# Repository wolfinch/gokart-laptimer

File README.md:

#Gokart-LapTimer-iMproved (GLTiM) 1.0
---------
The GLTiM is built on top of the gokart-laptimer which uses IR beacon and Raspbery Pi as detector/Receiver. 
The GLT improved provides many more features than the previous version plus a more streamlined web interface.

1. Two way RF communication using Nordic NRF24L01+ RF chip between Control center and detector
2. Detector Supports Magnetic Strip as well as IR beacon
3. Detector is in Kart. Allows feedback for the driver (not implemented)
4. Raspberry Pi as control Center 

# gokart-laptimer 0.1
Open hardware-software project to setup a go kart lap timer and counter with IR as the trigger beacon. 

1. NEC pulse width IR protocol is used as the beacon protocol. 
2. Raspberry-Pi based controller.
3. php based GUI.

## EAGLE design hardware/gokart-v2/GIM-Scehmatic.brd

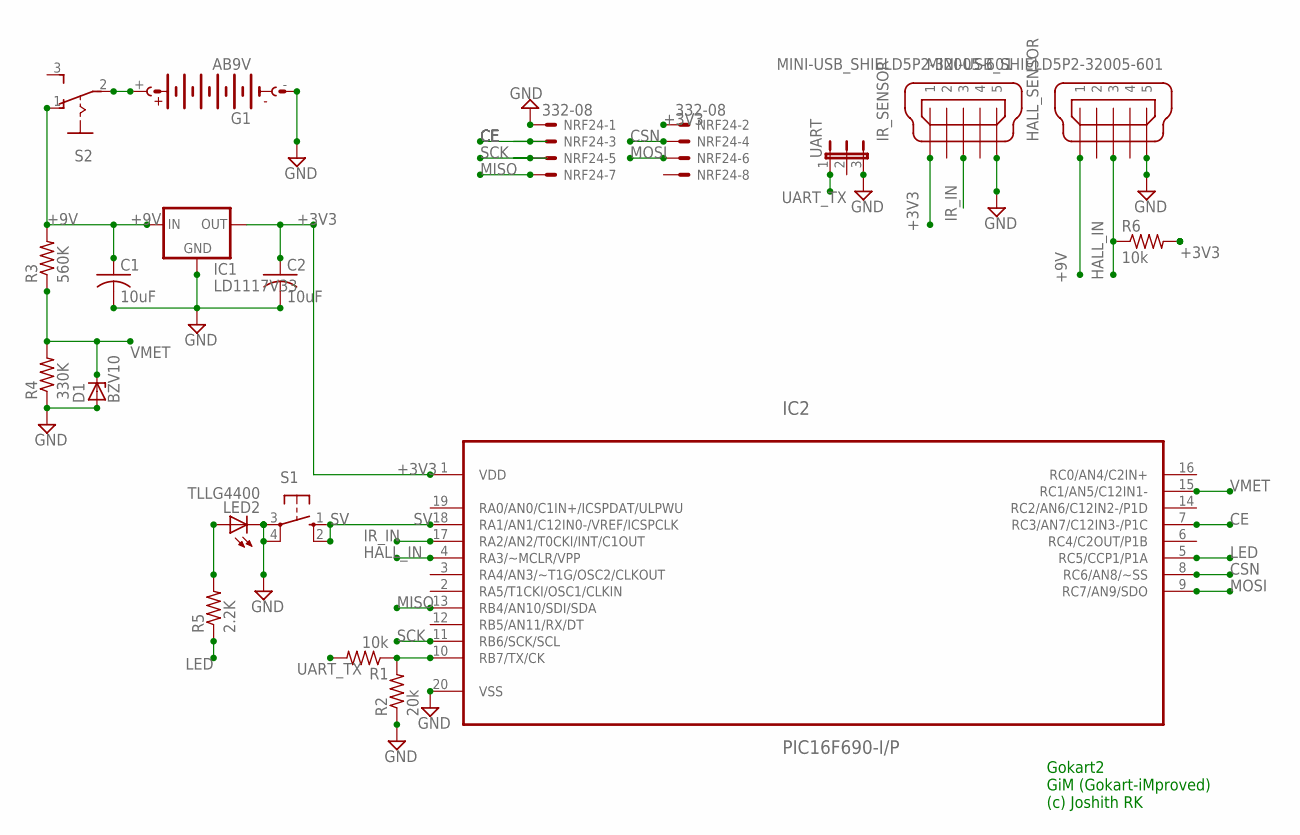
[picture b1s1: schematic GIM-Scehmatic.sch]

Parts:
C1, C2: 10uF; C025-040X050
D1: BZV10; DO34Z7
G1: AB9V
HALL_SENSOR: MINI-USB_SHIELD5P2-32005-601; 32005-601
IC1: LD1117V33
IC2: PIC16F690-I/P; DIP254P762X533-20
IR_SENSOR: MINI-USB_SHIELD5P2-32005-601; 32005-601
LED2: TLLG4400; LED3MM
NRF24: 332-08
R1, R6: 10k; 0204/7
R2: 20k; 0204/7
R3: 560K; 0204/7
R4: 330K; 0204/7
R5: 2.2K; 0204/7
S1: 10-XX; B3F-10XX
S2: M251
UART: JP2E; JP2

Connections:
+3V3: C2.1, IC1.OUT, IC2.1 (VDD), IR_SENSOR.1, NRF24.2, R6.2
+9V: C1.1, HALL_SENSOR.1, IC1.IN, R3.2, S2.1 (O)
CE: IC2.7 (RC3/AN7/C12IN3-/P1C), NRF24.3
CSN: IC2.8 (RC6/AN8/~SS), NRF24.4
GND: C1.2, C2.2, D1.A, G1.-, HALL_SENSOR.5, IC1.GND, IC2.20 (VSS), IR_SENSOR.5, LED2.K (C), NRF24.1, R2.1, R4.1, S1.3, S1.4 (P1), UART.3
HALL_IN: HALL_SENSOR.3, IC2.4 (RA3/~MCLR/VPP), R6.1
IR_IN: IC2.17 (RA2/AN2/T0CKI/INT/C1OUT), IR_SENSOR.3
LED: IC2.5 (RC5/CCP1/P1A), R5.1
MISO: IC2.13 (RB4/AN10/SDI/SDA), NRF24.7
MOSI: IC2.9 (RC7/AN9/SDO), NRF24.6
unnamed: IC2.10 (RB7/TX/CK), R1.1, R2.2
unnamed: G1.+, S2.2
unnamed: LED2.A, R5.2
SCK: IC2.11 (RB6/SCK/SCL), NRF24.5
SV: IC2.18 (RA1/AN1/C12IN0-/VREF/ICSPCLK), S1.1 (S), S1.2 (S1)
UART_TX: R1.2, UART.1
VMET: D1.C, IC2.15 (RC1/AN5/C12IN1-), R3.1, R4.2

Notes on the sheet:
Gokart2 GiM (Gokart-iMproved) (c) Joshith RK

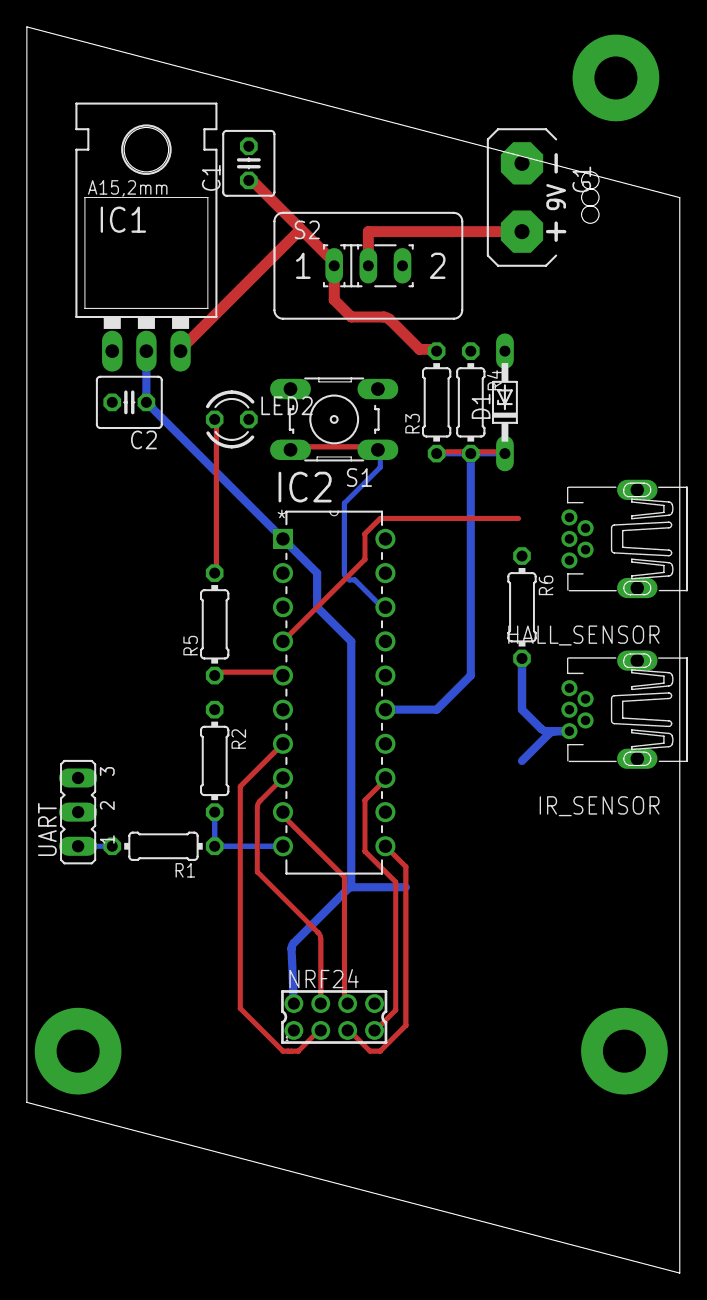
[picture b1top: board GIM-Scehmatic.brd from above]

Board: 2 copper layers, 48.6 x 92.7 mm, 19 parts (0 on the bottom side), 17 nets.

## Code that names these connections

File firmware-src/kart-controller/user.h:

/* 
 * File:   user.h
 * Author: joshith
 *
 * Created on 30 March, 2015, 5:33 PM
 */

#ifndef USER_H
#define	USER_H

#ifdef	__cplusplus
extern "C" {
#endif
/******************************************************************************/
/* User Level #define Macros                                                  */
/******************************************************************************/



// PIC16F690 Configuration Bit Settings

// 'C' source line config statements
#include <xc.h>
#include <stdint.h>         /* For uint8_t definition */

// #pragma config statements should precede project file includes.
// Use project enums instead of #define for ON and OFF.

// CONFIG
#pragma config FOSC = INTRCIO   // Oscillator Selection bits (INTOSCIO oscillator: I/O function on RA4/OSC2/CLKOUT pin, I/O function on RA5/OSC1/CLKIN)
#pragma config WDTE = OFF       // Watchdog Timer Enable bit (WDT disabled and can be enabled by SWDTEN bit of the WDTCON register)
#pragma config PWRTE = OFF      // Power-up Timer Enable bit (PWRT disabled)
#pragma config MCLRE = OFF      // MCLR Pin Function Select bit (MCLR pin function is digital input, MCLR internally tied to VDD)
#pragma config CP = OFF         // Code Protection bit (Program memory code protection is disabled)
#pragma config CPD = OFF        // Data Code Protection bit (Data memory code protection is disabled)
#pragma config BOREN = OFF      // Brown-out Reset Selection bits (BOR disabled)
#pragma config IESO = OFF       // Internal External Switchover bit (Internal External Switchover mode is disabled)
#pragma config FCMEN = OFF      // Fail-Safe Clock Monitor Enabled bit (Fail-Safe Clock Monitor is disabled)


#define _XTAL_FREQ 4000000			// 4MHz. required for delay Routines. 

/*
 * SPI_CONFIG for NRF24 Chip
 * ======================
 * MISO - RB4 (7), UART Rx
 * MOSI - RC7 (8), UART Tx
 * SCK - RB6 (9) , Dig o/p
 * CSN - RC6 (10), Dig o/p
 * CE  - RC3 (11),  Dig o/p
 * IRQ - ?????
 * 
 * Hall Sensor I/p (Can be connected to comp. Or Dig i/p through external comp)
 * ===============
 * RA2 (12) - IOC
 * 
 * Trigger Switch:
 * ===============
 * RA1 (13) - IOC (weak pullup)
 * 
 * Notif LED:
 * ==========
 * RC5 (18)
 *  
 */

#define TRISMOSI 	TRISCbits.TRISC7		//SPI_MOSI    
#define TRISMISO 	TRISBbits.TRISB4		//SPI_MISO
#define TRISUART_RX	TRISBbits.TRISB5		//UART_RX
#define TRISUART_TX	TRISBbits.TRISB7		//UART_TX    
#define TRISCSK 	TRISBbits.TRISB6		//SPI_CLK
#define TRISCSN 	TRISCbits.TRISC6		//SPI_CSN
#define TRISCE  	TRISCbits.TRISC3		//SPI_CE
    
#define MOSI 	PORTCbits.RC7		//SPI_MOSI    
#define MISO 	PORTBbits.RB4		//SPI_MISO
#define UART_RX	PORTBbits.RB5		//UART_RX
#define UART_TX	PORTBbits.RB7		//UART_TX    
#define CSK 	PORTBbits.RB6		//SPI_CLK
#define CSN 	PORTCbits.RC6		//SPI_CSN
#define CE  	PORTCbits.RC3		//SPI_CE

#define SENSOR_IR       PORTAbits.RA3       // IR Sensor connected (???) (to use IOC)     //FIXME: CLOCK IN, can't be used in LP
#define SENSOR_BATT     PORTAbits.RA0       // Battery level ind connected (9v) (ANSEL=1) //FIXME: CLOCK OUT, can't be used in LP
#define SENSOR_HALL  	PORTAbits.RA2		//Hall sensor input extINT available
#define KEY_1           PORTAbits.RA1		//Push Switch Key_1
        
#define IND_LED PORTCbits.RC5       // Indicator LED (OUT)
    
/*********TMR1 Time macros*********/
    /* The Fixed Frame beacon format uses Modified NEC code */
/* |---4MsPulse---|---2.5MsGap|--562uS(1)--|--562uS(0)--|--562uS(1)--|--1682uS(0)--|--562uS(1)--|*/
/* |--------Header------------|----------1--------------|------------0-------------|--Trailer---|*/  
/*
 * Each timer tick is 64uS. TMR0 is 8Bit MAX = 255
 * 20% signal Tolerance
 */    
#define TMR4mS   192      // 4MS, 62.5 Ticks, Preset TMR REg to Max - 62.5 => 255 - 63 
#define TMR2mS5  215      // 2.5Ms, 39.06 Ticks = 215     
#define TMR562uS 246           // 562uS (~564uS) = 8.96 => TMR0 = 246ticks, 
#define TMR1mS6  228           // 1.68Ms    = 26.25 Ticks, => 228
#if 0
    /* +10% */
#define TMR4mSHI   186      // 4.4MS, 68.75 Ticks, Preset TMR REg to Max - 69 => 186
#define TMR2mS5HI  212      // 2.75Ms, ~43 Ticks      
#define TMR562uSHI 245           // 620uS  = 10ticks, 
#define TMR1mS6HI  226           // 1.80Ms    = 29 Ticks, 

    /* -10% . Lower threshold = TMR1 Start + lo Ticks */ 
#define TMR4mSLO   242      // 3.6MS, 56 Ticks, Preset TMR REg to Max + 56 => 186 + 56 = 242   
#define TMR2mS5LO  247      // 2.25Ms, 35 Ticks = 247
#define TMR562uSLO 252           // 505uS (~564uS) = 7.9ticks, 
#define TMR1mS6LO  249          // 1.53Ms    = 23.9 Ticks, 
#endif
    /* +20% */
#define TMR4mSHI   180      // 4.8MS, 75 Ticks, Preset TMR REg to Max - 75 => 180
#define TMR2mS5HI  208      // 3Ms, ~47 Ticks      
#define TMR562uSHI 244           // 674.4uS  = 11ticks, 
#define TMR1mS6HI  223           // 2.02Ms    = 32 Ticks, 

    /* -20% . Lower threshold = TMR1 Start + lo Ticks */
#define TMR4mSLO   230      // 3.2MS, 50 Ticks, Preset TMR REg to Max + 50 => 180 + 50 = 230   
#define TMR2mS5LO  239      // 2.0Ms, 31 Ticks = 239
#define TMR562uSLO 251           // 449uS = 7.01ticks, 
#define TMR1mS6LO  244          // 1.344Ms    = 21 Ticks, 
#define TMR1mS6LO562  230          // 1.344Ms    = 21 Ticks,     
    
/*********TMR1 Time macros*********/
	
/******************************************************************************/
/* User Function Prototypes                                                   */
/******************************************************************************/

/* TODO User level functions prototypes (i.e. InitApp) go here */

void InitApp(void);         /* I/O and Peripheral Initialization */

void handleSwitch(void);

void handleIRSignal(void);

void blinkLed(unsigned short blinks);

uint8_t read_battery_level (void);

#if 0
#ifndef TMR1RESTART
#define TMR1RESTART(tmrL, tmrH) \
            do{          \
                TMR1L = tmrL; \
                TMR1H = tmrH;  \
                PIR1bits.TMR1IF  = 0; \
                PIE1bits.TMR1IE  = 1; \
                T1CONbits.TMR1ON = 1; \
            } while(0);//           -->> On
#endif        
#endif
#ifdef	__cplusplus
}
#endif

#define MAX_PAYLOAD_COUNT 8
extern volatile uint8_t     data_valid_bitmap;
#define data_set(x) (data_valid_bitmap |= (1<<(x)))
#define data_unset(x) (data_valid_bitmap &= ~(1<<(x)))
#define is_data_valid(x) (data_valid_bitmap & (1<<(x)))
#define data_ready() (data_valid_bitmap)
#define data_q_flush() (data_valid_bitmap = 0)

typedef enum gim_detect_type_ {
     IR = 0,
     HALL
}gim_detect_type;

typedef struct gim_timeval_ {
    uint16_t sec;       // 1/2sec epoch counter
    uint8_t  m_sec;     // 2mS counter
}gim_timeval;

typedef struct gim_kart_data_ {
    gim_timeval    time;    
    uint8_t     battery_level;
    uint8_t     dev_id        :5;
    uint8_t     detect_type   :1;
    uint8_t     detect_code   :2;   //Used for IR code, section detection
    uint8_t     lap_count     :6;   // supports max 64 laps before wraparound
    uint8_t     seed          :2;   //randomness. To avoid h/w dropping the packet in case of resend
}kart_data_t;

#endif	/* USER_H */

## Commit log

2015-04-25 moved pic firmware files to own dir
2015-04-25 commit for gokart-web interface and RPi code
2015-04-25 bug fix: wrong kartid causes logging failure
2015-04-25 bug fix: button id stripping needed
2015-06-04 Directory changes for IRXmit firmware code
2015-06-04 renamed the irbeacon
2015-06-04 Added files for gokart-controller
    This adds the functionality with intelligent in-kart controller.
    Support magnetic strip and IR beacon on the track. Sends the detection
    data to the rPi controller off-track reliably through RF radio
2015-06-04 created dir for rpi components of version-2 (in-kart based) system
2015-06-04 new source files for gokartd-v2
2015-06-04 added hardware related files
    gokart-controller schematic and board files. Created using eagle
2015-06-04 changes in eagle .epf
2015-06-05 IR and hall sensor optimizations
2015-06-06 Fixed IR interrupt timing
2015-06-06 multi Segment support with IR codes
    upto 4 Segments (IR based) are supported with 2 bit IR code
2015-06-08 multisection support, bugfixes, optimizations
2015-06-08 lap-time calculation logic implementation
2015-06-09 gokart controller file ops implementation, log implementation, bugfixes
2015-06-15 initial web interface changes to support v2
2015-06-15 logical changes in web and install script
2015-06-16 web related changes to support multiple sensors etc.
2015-06-18 web interface changes for battery level and lap counts on control panel
2015-06-21 Major design changes in timer handling across firmware, software and web.
    With this changes, time stamp is stored, which is adjusted across
    wraparound. Firmware sends Lap number and a seed to protect loosing lap
    count in case a lap is missed.
2015-06-22 Firmware changes in data handling
    Efficiency and reliability improvements for multiple data handling.
    Design change.
2015-06-22 Lap number wraparound logic fix
2015-06-25 Cleanup
2015-06-29 Major rework in web. Added support for historical data
2015-07-06 Final set of changes in IR Beacon for the PCB
2015-08-01 stream lining 1
2015-08-05 stream lining
2015-08-08 release point
2015-08-09 release - 1
